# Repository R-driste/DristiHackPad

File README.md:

# DroydPad
Here is my hackpad for Athena/Highway in Hack Club! It includes 12 switches, an oled and a rotary encoder.
- You can find the pcb gerbers and 3d print files in the sub folders. Please print my case white so I can paint it later.
- My firmware turns the hackpad into a T-9 typing pad or a shortcuts simplifier (don't have to hold down multiple keys at once). The OLED displays what is currently happening and the rotary encoder changes the brightness of the screen.
- Pictures of my schematic and cad can be found in the general_files

# Case CAD
Used Autodesk Fusion. In the cad_files folder I have attached my main cad file, my components (including the files needed to print the case) and components I borrowed from online (credits are below).

# Schematic for PCB
- I designed the PCB in Kicad. In the kicad folder of the repository I attached my primary project files for the PCB.

## BOM:
These should be the necessary parts to assemble this project.
#### From Kit
- 1x Seeed Studio Xiao RP2040
- 1x EC11E Rotary Encoder
- 1x 0.91" SSD1306 OLED screen
- 12x Cherry MX style switches
- 12x Blank DSA keycaps (white, will color)
- 12x DO-35 diodes
- 4x M3x16mm screws
- 4x M3x5mx4mm heatset inserts

#### For Print
- 1x Base Frame of Case
- 1x Top Cover of Case
- 1x Rotary Encoder Knob

+ the PCB of course.

## CREDITS
Online Components Links:
Cherry MX Switch Model -> https://grabcad.com/library/cherry-mx-red-switch-1 by Baco
DSA Keycap Model -> https://grabcad.com/library/dsa-keycap-for-cherry-mx-switches-1 by zim cad
USB-C Connector Model -> https://grabcad.com/library/usb-c-bulkhead-connector-1 by Nelson Stoldt
EC11 Rotary Encoder Model -> https://grabcad.com/library/ec11-rotary-encoder-with-switch-1 by Anthony Berkow
EC11 Rotary Encoder Knob Model -> https://www.printables.com/model/1000044-ec11-encoder-knob/files by Kea Workshop
Xiao Model -> https://grabcad.com/library/seeed-studio-xiao-rp2040-1 by mirac gulgonul
OLED 0.91 128x32 Model -> https://grabcad.com/library/oled-0-91-128x32-1 by Stilet Fox

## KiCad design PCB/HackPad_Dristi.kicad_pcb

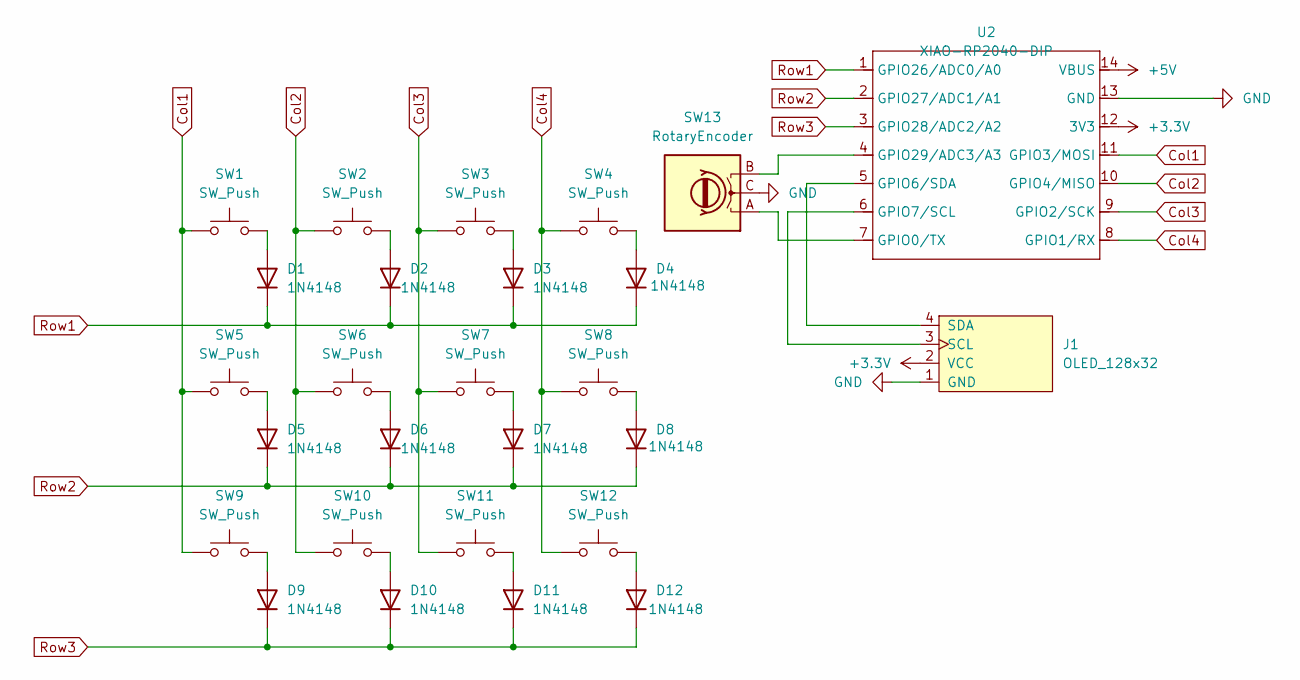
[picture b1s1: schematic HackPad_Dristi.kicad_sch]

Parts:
D1, D2, D3, D4, D5, D6, D7, D8, D9, D10, D11, D12: 1N4148; D_DO-35_SOD27_P2.54mm_Vertical_AnodeUp
J1: OLED_128x32
SW1, SW2, SW3, SW4, SW5, SW6, SW7, SW8, SW9, SW10, SW11, SW12: SW_Push; SW_Cherry_MX_1.00u_PCB
SW13: RotaryEncoder; RotaryEncoder_Alps_EC11E_Vertical_H20mm_CircularMountingHol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
U2: XIAO-RP2040-DIP

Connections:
+3.3V: J1.2 (VCC), U2.12 (3V3)
+5V: U2.14 (VBUS)
Col1: SW1.1, SW5.1, SW9.1, U2.11 (GPIO3/MOSI)
Col2: SW2.1, SW6.1, SW10.1, U2.10 (GPIO4/MISO)
Col3: SW3.1, SW7.1, SW11.1, U2.9 (GPIO2/SCK)
Col4: SW4.1, SW8.1, SW12.1, U2.8 (GPIO1/RX)
GND: J1.1 (GND), SW13.C, U2.13 (GND)
unnamed: D1.2 (A), SW1.2
unnamed: D2.2 (A), SW2.2
unnamed: D3.2 (A), SW3.2
unnamed: D4.2 (A), SW4.2
unnamed: D5.2 (A), SW5.2
unnamed: D6.2 (A), SW6.2
unnamed: D7.2 (A), SW7.2
unnamed: D8.2 (A), SW8.2
unnamed: D9.2 (A), SW9.2
unnamed: D10.2 (A), SW10.2
unnamed: D11.2 (A), SW11.2
unnamed: D12.2 (A), SW12.2
unnamed: J1.3 (SCL), U2.6 (GPIO7/SCL)
unnamed: J1.4 (SDA), U2.5 (GPIO6/SDA)
unnamed: SW13.A, U2.7 (GPIO0/TX)
unnamed: SW13.B, U2.4 (GPIO29/ADC3/A3)
Row1: D1.1 (K), D2.1 (K), D3.1 (K), D4.1 (K), U2.1 (GPIO26/ADC0/A0)
Row2: D5.1 (K), D6.1 (K), D7.1 (K), D8.1 (K), U2.2 (GPIO27/ADC1/A1)
Row3: D9.1 (K), D10.1 (K), D11.1 (K), D12.1 (K), U2.3 (GPIO28/ADC2/A2)

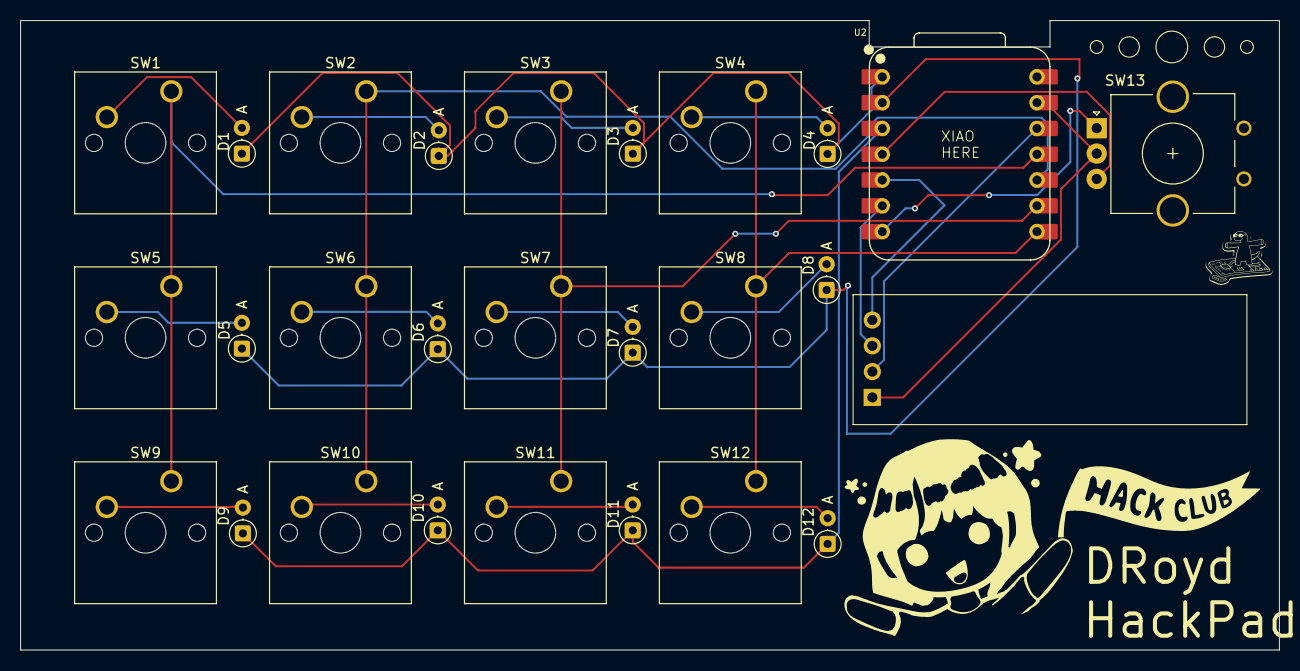
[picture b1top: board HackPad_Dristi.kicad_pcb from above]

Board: 2 copper layers, 124.0 x 62.0 mm, 27 parts (0 on the bottom side), 25 nets.

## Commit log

2025-06-27 Add files via upload
    kicad add
2025-06-27 Rename HackPad_Dristi.kicad_prl to kicad/HackPad_Dristi.kicad_prl
2025-06-27 Rename HackPad_Dristi.kicad_pcb to kicad/HackPad_Dristi.kicad_pcb
2025-06-27 Rename HackPad_Dristi.kicad_pro to kicad/HackPad_Dristi.kicad_pro
2025-06-27 Rename HackPad_Dristi.kicad_sch to kicad/HackPad_Dristi.kicad_sch
2025-06-28 update components
2025-06-28 readme update
2025-06-29 added firmware
2025-06-29 Save local changes before pull
2025-06-29 adjust
2025-06-30 firmware update
2025-06-30 restyled
2025-06-30 readme changes
2025-07-05 updated format
2025-07-05 update code
